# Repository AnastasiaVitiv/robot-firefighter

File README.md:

An autonomous robot built on the STM32F103 microcontroller designed for searching and automatically extinguishing fire hazards. The system detects hotspots using a thermal imaging camera, verifies target distance with a laser ToF rangefinder, and aims a pan-tilt turret equipped with a water pump.

Here is a link to a video of it.
https://drive.google.com/drive/folders/1A6Z49xJr-joiZc6H49M-nv8G-IkJ48fF?usp=sharing

Components:

Microcontroller: STM32F103C8T6.
Thermal Camera: Melexis MLX90640.
Rangefinder: VL53L1X.
Pan-Tilt Turret (2-DOF): MG995 servos driven by hardware PWM.
Extinguishing System: 5V water pump controlled via an N-channel MOSFET with flyback diode protection.
Power Supply: 2S Li-Ion battery  with step-down DC-DC converters.

Hardware Architecture & Technical Details

1. PWM Configuration
An STM32 hardware timer is used to generate 50 Hz PWM signals for servo control:
Prescaler (PSC): 35 each tick equals 1ms.
Auto-Reload Register (ARR):19999 20000ms.

2. I2C Bus Interface
Both the MLX90640 thermal camera and VL53L1X  rangefinder share the same I2C bus.
External 4.7 kOm pull-up resistors to 3.3 V ensure clean signal rise times at 400 kHz.

System Logic Flow

1.Scanning:
The STM32 reads frame data from the MLX90640 over I2C and locates the peak pixel temperature.
2.Thresholding:
If T_max > 150°C, the system calculates the angular offset of the target relative to the frame center.
3.Targeting:
Offset values update the timer's CCR registers, rotating the servo turret toward the heat source.
4. Distance Measurement & Pitch Adjustment:
The VL53L1X sensor measures the distance to the target:
   If Distance > 20 cm: The top servo tilts UP by 6° to compensate for water trajectory arc.
   If Distance > 15 cm (15–20 cm): The top servo tilts UP by 4°.
   If Distance < 15 cm: No pitch angle offset applied.
5. Suppression:The pump operates for a 5s burst, followed by a rescan to verify fire suppression.

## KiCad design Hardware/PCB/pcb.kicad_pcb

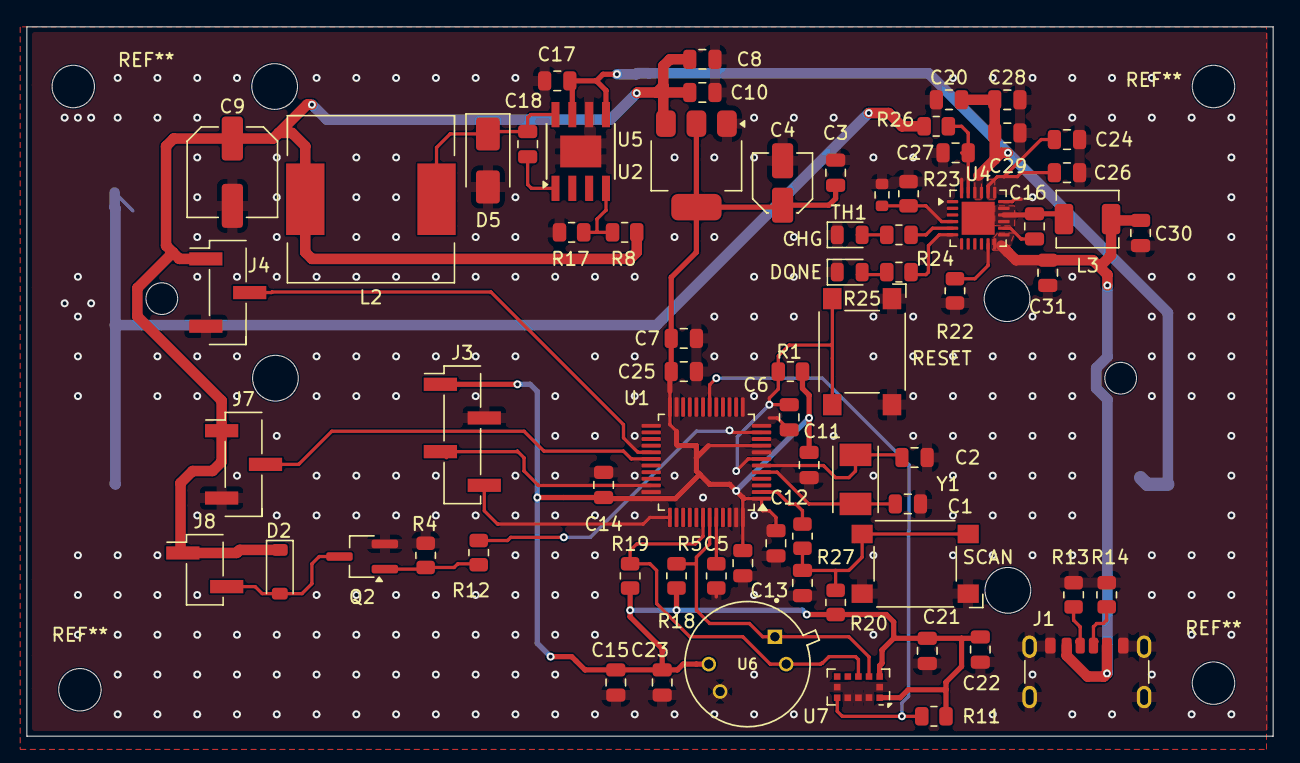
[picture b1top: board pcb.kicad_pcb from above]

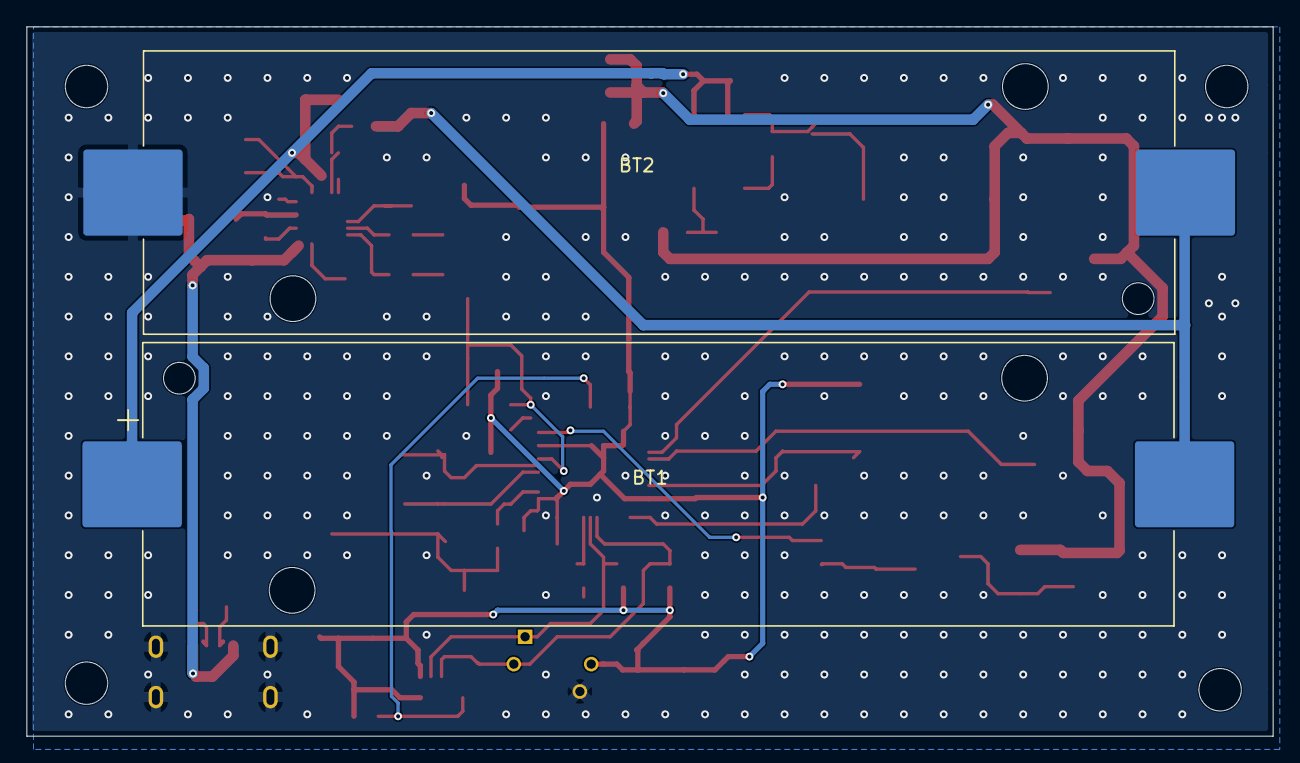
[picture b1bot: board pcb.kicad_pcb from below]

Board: 2 copper layers, 94.0 x 53.5 mm, 72 parts (2 on the bottom side), 37 nets.

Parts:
BT1, BT2: 18650; BatteryHolder_Keystone_1042_1x18650
C1, C2: 20pF; C_0805_2012Metric
C3, C5, C6, C7, C8, C11, C12, C13, C14, C15, C16, C20, C21, C27: 0.1uF; C_0805_2012Metric
C4: 22uF; C_Elec_4x5.4
C9: 220uF; C_Elec_6.3x7.7
C10, C17, C23, C25, C28, C29, C30, C31: 10uF; C_0805_2012Metric
C18: 0.01uF; C_0805_2012Metric
C22: 4.7uF; C_0805_2012Metric
C24, C26: 22uF; C_0805_2012Metric
CHG: LED; LED_0805_2012Metric
D2: 1N4007; D_SOD-123
D5: SS34; D_SMA
DONE: LED; LED_0805_2012Metric
J1: USB_C_Receptacle_PowerOnly_6P; USB_C_Receptacle_GCT_USB4125-xx-x_6P_TopMnt_Horizontal
J3: ST-Link; PinHeader_1x04_P2.54mm_Vertical_SMD_Pin1Left
J4: ServoX; PinHeader_1x03_P2.54mm_Vertical_SMD_Pin1Left
J7: ServoY; PinHeader_1x03_P2.54mm_Vertical_SMD_Pin1Left
J8: Pump; PinHeader_1x02_P2.54mm_Vertical_SMD_Pin1Left
L2: 22uH; L_12x12mm_H8mm
L3: 2.2uH; L_TechFuse_SL0420
Q2: AO3400A; TSOT-23_HandSoldering
R1, R5, R8, R11, R20, R26: 10kOm; R_0805_2012Metric
R4: 100kOm; R_0805_2012Metric
R12, R27: 1kOm; R_0805_2012Metric
R13, R14: 5.1kOm; R_0805_2012Metric
R17: 3.3kOm; R_0805_2012Metric
R18, R19: 4.7kOm; R_0805_2012Metric
R22: 91kOm; R_0805_2012Metric
R23: 82kOm; R_0805_2012Metric
R24, R25: 330Om; R_0805_2012Metric
RESET: SW_Push; SW_SPST_Omron_B3FS-100xP
SCAN: SW_Push; SW_SPST_Omron_B3FS-100xP
TH1: 100kOm; R_0603_1608Metric
U1: STM32F103C8Tx; LQFP-48_7x7mm_P0.5mm
U2: AMS1117-3.3; SOT-223-3_TabPin2
U4: ip2326; QFN-24-1EP_4x4mm_P0.5mm_EP2.5x2.5mmsolid thermal pad
U5: TPS5430DDA; TI_SO-PowerPAD-8
U6: MLX90640ESF-BAB-000-SP; TO292P945H1165-4
U7: VL53L0CXV0DH1; ST_VL53L0X
Y1: 8MHz; Crystal_SMD_TXC_7A-2Pin_5x3.2mm

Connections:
5V_USB: C30.1, C31.1, J1.A9 (VBUS), J1.B9 (VBUS), L3.2, U4.12, U4.13
+3.3V: C3.1, C4.1, C5.2, C7.2, C11.2, C12.2, C14.2, C15.1, C21.2, C22.2, C23.1, C25.2, J3.1, R1.1, R11.1, R18.1, R19.1, R20.1, U1.1 (VBAT), U1.9 (VDDA), U1.24 (VDD), U1.36 (VDD), U1.48 (VDD), U2.2 (VO), U6.2 (VDD), U7.1 (AVDDVCSEL), U7.11 (AVDD)
+5V: C8.1, C9.1, C10.1, D2.1 (K), J4.1, J7.1, J8.1, L2.2, R8.2, U2.3 (VI)
B+: BT1.1 (+), C17.1, C20.2, C28.1, C29.1, U4.21 (VOUT), U4.22 (VOUT), U5.5 (EN), U5.7 (VIN)
B-: BT2.2 (-), C1.1, C2.1, C3.2, C4.2, C5.1, C6.2, C7.1, C8.2, C9.2, C10.2, C11.1, C12.1, C13.1, C14.1, C15.2, C17.2, C20.1, C21.1, C22.1, C23.2, C24.2, C25.1, C26.2, C27.1, C28.2, C29.2, C30.2, C31.2, CHG.1 (K), D5.2 (A), DONE.1 (K), J1.A12 (GND), J1.B12 (GND), J1.SH (SHIELD), J3.2, J4.3, J7.3, Q2.2 (S), R4.2, R5.2, R13.2, R14.2, R17.1, R22.1, R23.1, RESET.1, SCAN.1, TH1.1, U1.8 (VSSA), U1.23 (VSS), U1.35 (VSS), U1.47 (VSS), U2.1 (GND), U4.18 (PGND), U4.24 (VBATG), U5.6 (GND), U5.9 (GNDPAD), U6.3 (GND), U7.2 (AVSSVCSEL), U7.3 (GND), U7.4 (GND), U7.6 (GND), U7.12 (GND)
BTN_SCAN: C13.2, R20.2, R27.1, SCAN.2
I2C1_SCL: R19.2, U1.42 (PB6), U6.4 (SCL), U7.9 (SDA)
I2C1_SDA: R18.2, U1.43 (PB7), U6.1 (SDA), U7.10 (SCL)
MID: BT1.2 (-), BT2.1 (+), R26.1
unnamed: C16.1, L3.1, U4.15 (LX), U4.16 (LX), U4.17 (LX)
unnamed: C24.1, C26.1, U4.19 (VSYS), U4.20 (VSYS)
unnamed: D2.2 (A), J8.2, Q2.3 (D)
unnamed: DONE.2 (A), R25.2
unnamed: C18.1, D5.1 (K), L2.1, U5.8 (PH)
unnamed: CHG.2 (A), R24.2
unnamed: J1.A5 (CC1), R13.1
unnamed: J1.B5 (CC2), R14.1
unnamed: Q2.1 (G), R4.1, R12.2
unnamed: R5.1, U1.44 (BOOT0)
unnamed: C6.1, R1.2, RESET.2, U1.7 (NRST)
unnamed: J3.3, U1.34 (PA13)
unnamed: J3.4, U1.37 (PA14)
unnamed: R27.2, U1.2 (PC13)
unnamed: C1.2, U1.5 (PD0), Y1.1
unnamed: C2.2, U1.6 (PD1), Y1.2
unnamed: R24.1, U4.5 (BAT_STAT)
unnamed: C16.2, U4.14
unnamed: R22.2, U4.11
unnamed: R25.1, U4.6
unnamed: R23.2, TH1.2, U4.4
unnamed: C27.2, R26.2, U4.23 (VBATM)
unnamed: C18.2, U5.1 (BOOT)
unnamed: R8.1, R17.2, U5.4 (VSENSE)
PUMP_GPIO: R12.1, U1.11 (PA1)
PWM_X: J4.2, U1.29 (PA8)
PWM_Y: J7.2, U1.30 (PA9)
VL53L1X_XSHUT: R11.2, U1.18 (PB0), U7.5 (XSHUT)

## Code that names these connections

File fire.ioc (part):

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Mcu.Name=STM32F103C(8-B)Tx
Mcu.Package=LQFP48
Mcu.UserName=STM32F103C8Tx
PA1.GPIOParameters=GPIO_PuPd
PA1.GPIO_PuPd=GPIO_PULLDOWN
PA1.Signal=GPIO_Output
PA13.Mode=Serial_Wire
PA13.Signal=SYS_JTMS-SWDIO
PA14.Mode=Serial_Wire
PA14.Signal=SYS_JTCK-SWCLK
PA8.Signal=S_TIM1_CH1
PA9.Signal=S_TIM1_CH2
PB0.GPIOParameters=PinState
PB0.PinState=GPIO_PIN_SET
PB0.Signal=GPIO_Output
PB6.Mode=I2C
PB6.Signal=I2C1_SCL
PB7.Mode=I2C
PB7.Signal=I2C1_SDA
PC13-TAMPER-RTC.GPIOParameters=GPIO_PuPd,GPIO_ModeDefaultEXTI
PC13-TAMPER-RTC.GPIO_ModeDefaultEXTI=GPIO_MODE_IT_FALLING
PC13-TAMPER-RTC.GPIO_PuPd=GPIO_PULLUP
PC13-TAMPER-RTC.Signal=GPXTI13
RCC.SYSCLKFreq_VALUE=36000000
RCC.SYSCLKSource=RCC_SYSCLKSOURCE_PLLCLK
board=custom
